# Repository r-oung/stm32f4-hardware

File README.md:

# Electronics EAGLE
A collection of [EAGLE](http://eagle.autodesk.com/) PCB projects.

## Organization
```
stm32f4-hardware       Root directory
├── assets             Custom EAGLE assets
|   ├── cam            CAM jobs
|   ├── dru            Design rules
|   ├── lbr            Libraries
|   ├── scr            Scripts
│   └── ulp            User language programs
└── prj                Projects
```

## Setup
In EAGLE's Control Panel, select `Options` > `Directories` and re-assign all directories with the ones in this repository.

## Licenses
Unless otherwise indicated in the file and/or folder, all files are licensed under [Creative Commons - Attribution 4.0 International (CC BY 4.0)](https://creativecommons.org/licenses/by/4.0/).

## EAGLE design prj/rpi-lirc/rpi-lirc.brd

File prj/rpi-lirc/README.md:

# Raspberry Pi LIRC Transceiver
A simple IR receiver and transceiver for the Raspberry Pi.

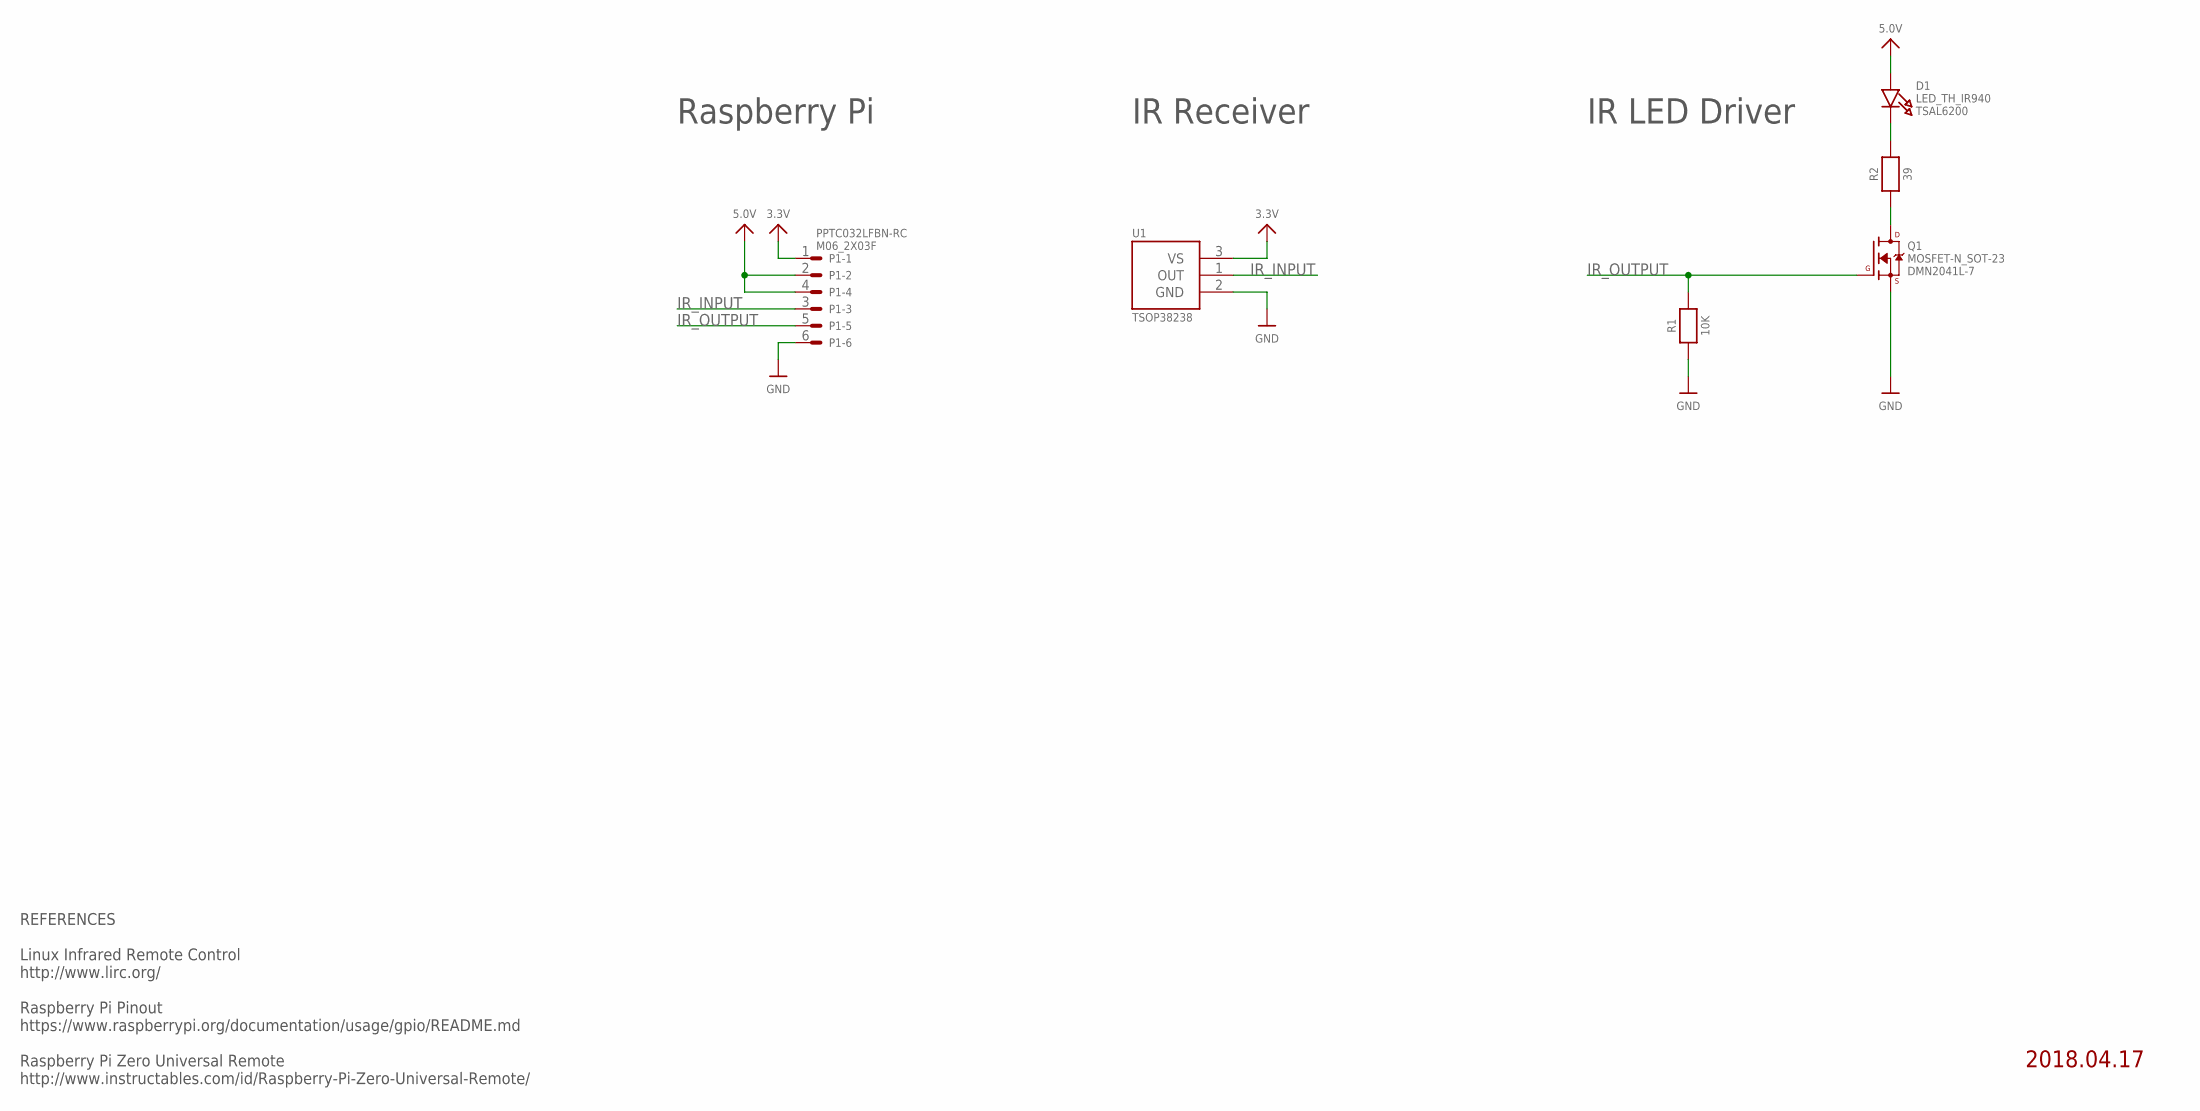
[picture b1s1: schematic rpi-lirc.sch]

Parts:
D1: LED_TH_IR940; RADIAL_5MM
P1: M06_2X03F; 2X03_LOCK
Q1: MOSFET-N_SOT-23; SOT23-3
R1: 10K; 0603
R2: 39; 0603
U1: TSOP38238

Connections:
3.3V: P1.1, U1.3 (VS)
5.0V: D1.A, P1.2, P1.4
GND: P1.6, Q1.2 (S), R1.1, U1.2 (GND)
IR_INPUT: P1.3, U1.1 (OUT)
IR_OUTPUT: P1.5, Q1.1 (G), R1.2
unnamed: D1.C, R2.2
unnamed: Q1.3 (D), R2.1

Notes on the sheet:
IR LED Driver
IR Receiver
Raspberry Pi
REFERENCES Linux Infrared Remote Control http://www.lirc.org/ Raspberry Pi Pinout https://www.raspberrypi.org/documentation/usage/gpio/README.md Raspberry Pi Zero Universal Remote http://www.instructables.com/id/Raspberry-Pi-Zero-Universal-Remote/
2018.04.17

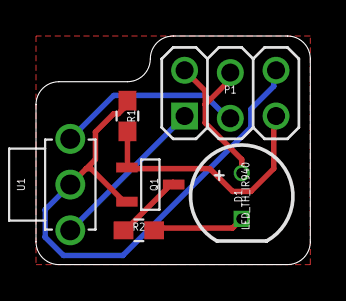
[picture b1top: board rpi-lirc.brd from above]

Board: 2 copper layers, 15.2 x 12.7 mm, 6 parts (0 on the bottom side), 7 nets.

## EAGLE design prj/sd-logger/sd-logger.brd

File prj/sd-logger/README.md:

# SD Logger
A tool for logging UART and CAN-bus data to an SD card.

The firmware for this project can be found in the [stm32f4-firmware repository](https://github.com/r-oung/stm32f4-firmware).

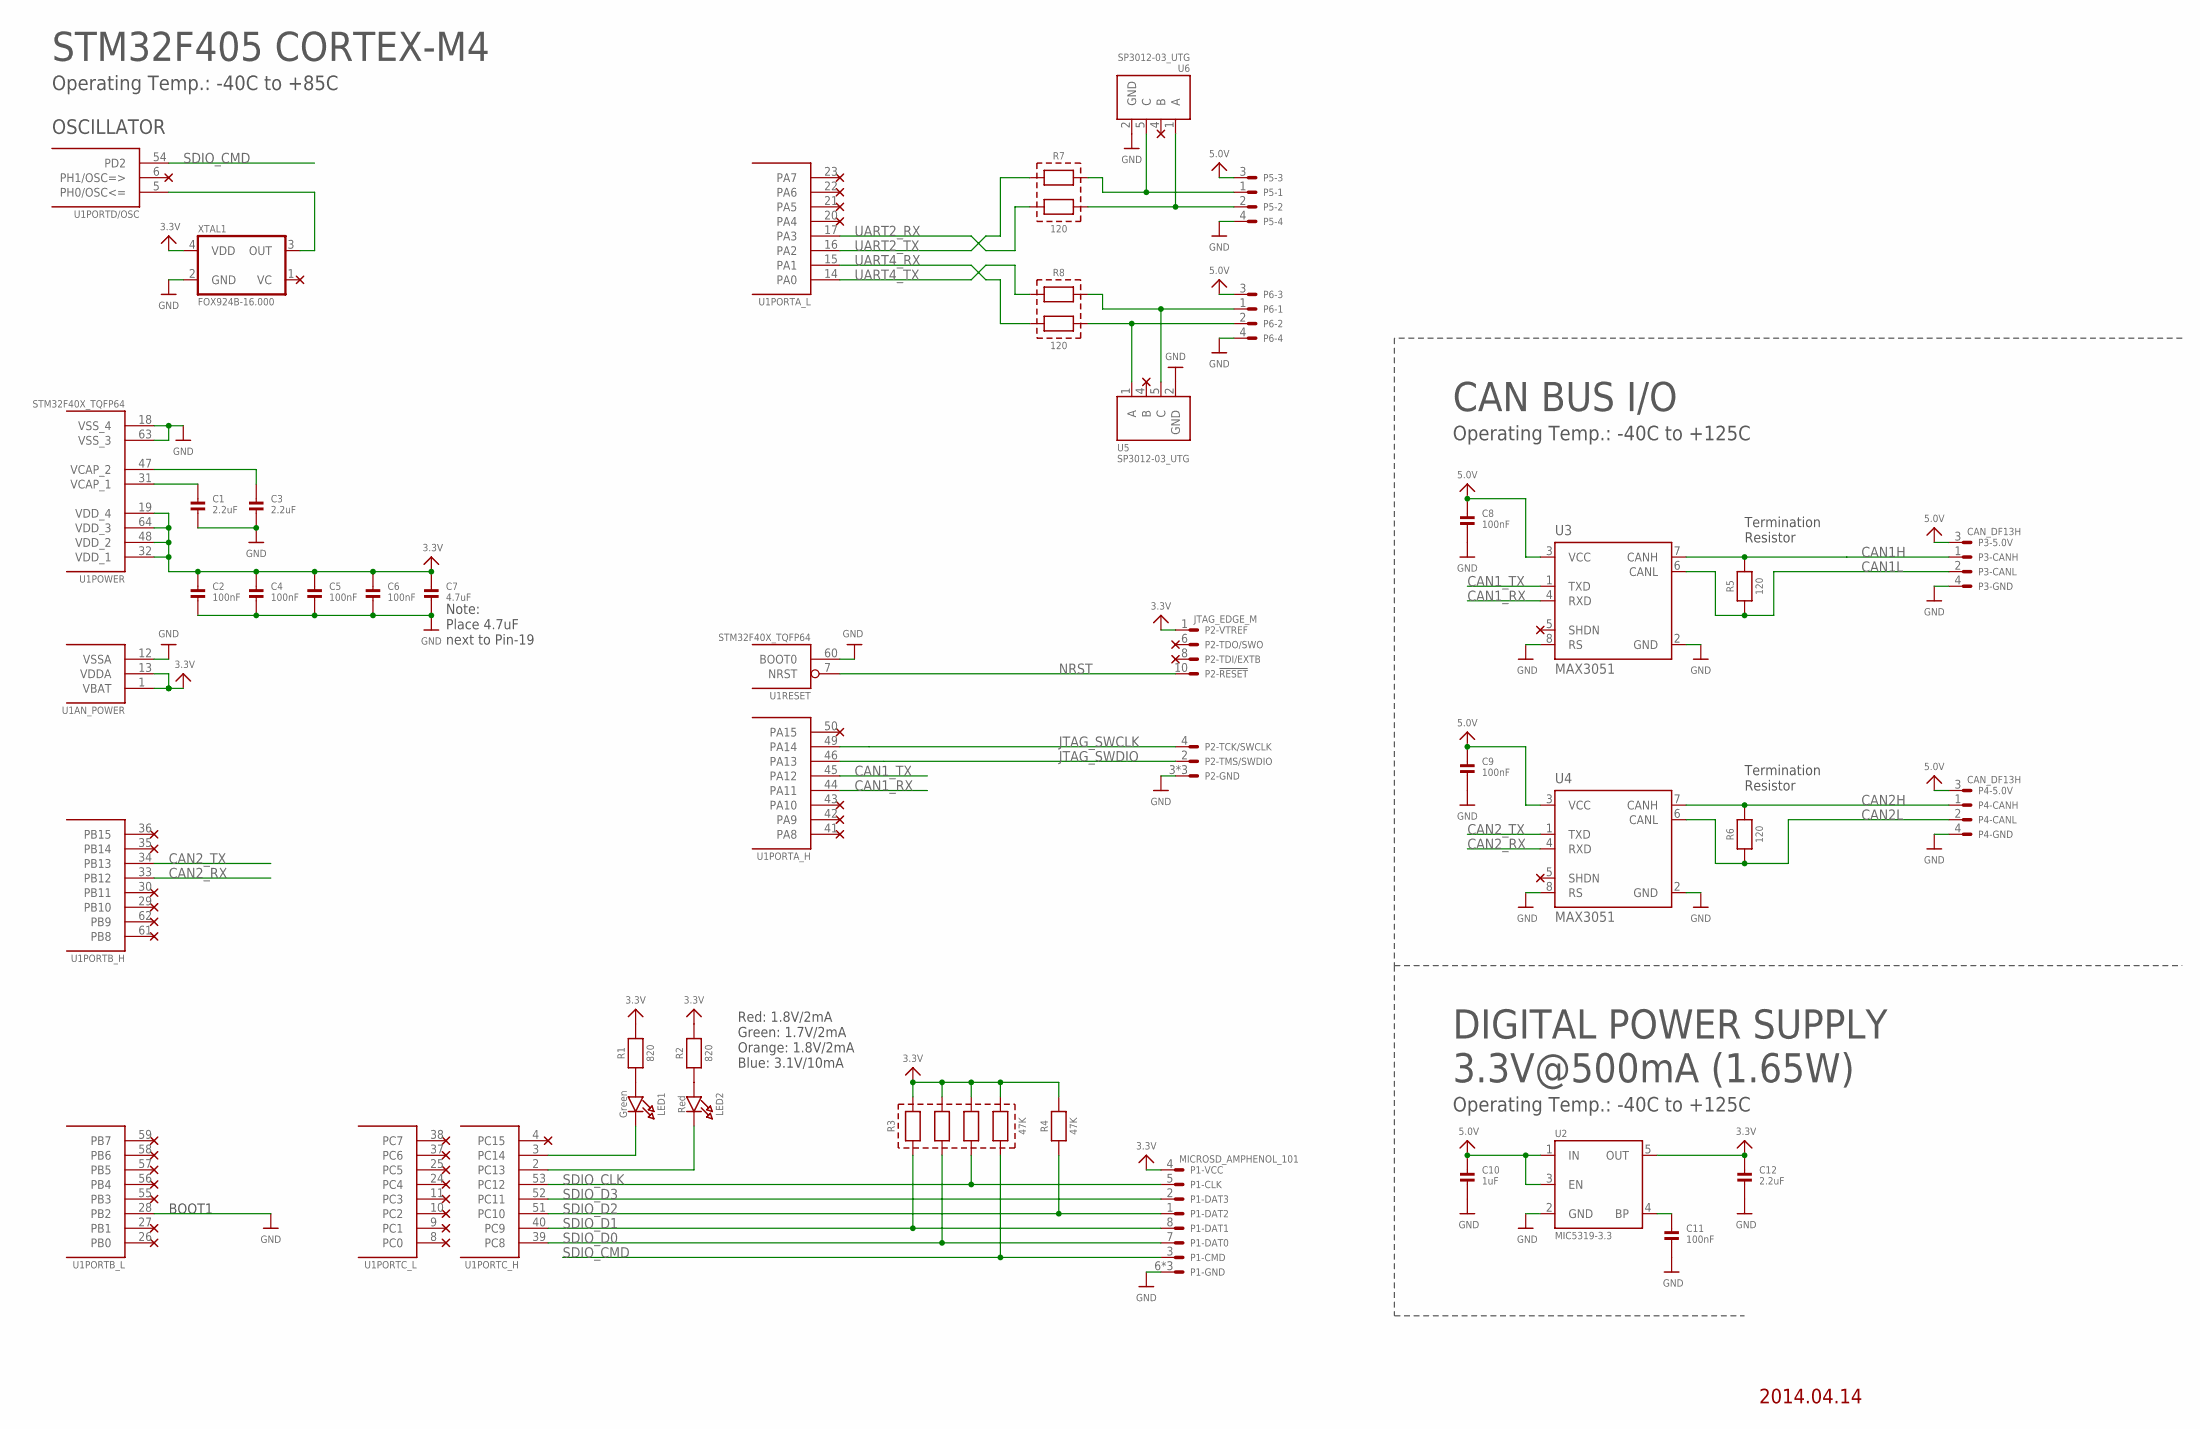
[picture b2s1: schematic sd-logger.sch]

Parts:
C1, C3, C12: 2.2uF; 0402
C2, C4, C5, C6, C8, C9, C11: 100nF; 0402
C7: 4.7uF; 0402
C10: 1uF; 0402
LED1: Green; CHIPLED_0603
LED2: Red; CHIPLED_0603
P1: MICROSD_AMPHENOL_101; AMPHENOL_101-00660-68
P2: JTAG_EDGE_M; FTSH-105-01-XXX-DV-EDGE
P3, P4: CAN_DF13H; DF13A-4P-1.25H
P5, P6: M04_DF13H; DF13A-4P-1.25H
R1, R2: 820; 0402
R3: 47K; EXBV8V
R4: 47K; 0402
R5, R6: 120; 0603
R7, R8: 120; EXBV4V
U1: STM32F40X_TQFP64; TQFP64
U2: MIC5319-3.3; SOT23-5
U3, U4: MAX3051; SOT23-8
U5, U6: SP3012-03_UTG; UDFN06
XTAL1: FOX924B-16.000; OSCILLATOR-5.0X3.2

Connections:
3.3V: C2.1, C4.1, C5.1, C6.1, C7.1, C12.1, P1.4, P2.1, R1.2, R2.2, R3.5, R3.6, R3.7, R3.8, R4.2, U1.1 (VBAT), U1.13 (VDDA), U1.19 (VDD_4), U1.32 (VDD_1), U1.48 (VDD_2), U1.64 (VDD_3), U2.5 (OUT), XTAL1.4 (VDD)
5.0V: C8.1, C9.1, C10.1, P3.3, P4.3, P5.3, P6.3, U2.1 (IN), U2.3 (EN), U3.3 (VCC), U4.3 (VCC)
CAN1H: P3.1, R5.2, U3.7 (CANH)
CAN1L: P3.2, R5.1, U3.6 (CANL)
CAN1_RX: U1.44 (PA11), U3.4 (RXD)
CAN1_TX: U1.45 (PA12), U3.1 (TXD)
CAN2H: P4.1, R6.2, U4.7 (CANH)
CAN2L: P4.2, R6.1, U4.6 (CANL)
CAN2_RX: U1.33 (PB12), U4.4 (RXD)
CAN2_TX: U1.34 (PB13), U4.1 (TXD)
GND: C1.2, C2.2, C3.2, C4.2, C5.2, C6.2, C7.2, C8.2, C9.2, C10.2, C11.2, C12.2, P1.6, P1.GND1, P1.GND3, P2.3, P2.5, P2.9, P3.4, P4.4, P5.4, P6.4, U1.12 (VSSA), U1.18 (VSS_4), U1.28 (PB2), U1.60 (BOOT0), U1.63 (VSS_3), U2.2 (GND), U3.2 (GND), U3.8 (RS), U4.2 (GND), U4.8 (RS), U5.2 (GND), U6.2 (GND), XTAL1.2 (GND)
JTAG_SWCLK: P2.4, U1.49 (PA14)
JTAG_SWDIO: P2.2, U1.46 (PA13)
unnamed: P5.2, R7.3, U6.1 (A)
unnamed: LED1.C, U1.3 (PC14)
unnamed: U1.5 (PH0/OSC<=), XTAL1.3 (OUT)
unnamed: C11.1, U2.4 (BP)
unnamed: P5.1, R7.4, U6.5 (C)
unnamed: P6.2, R8.3, U5.1 (A)
unnamed: P6.1, R8.4, U5.5 (C)
unnamed: LED2.C, U1.2 (PC13)
unnamed: LED2.A, R2.1
unnamed: LED1.A, R1.1
NRST: P2.10, U1.7 (NRST)
SDIO_CLK: P1.5, R3.3, U1.53 (PC12)
SDIO_CMD: P1.3, R3.4, U1.54 (PD2)
SDIO_D0: P1.7, R3.2, U1.39 (PC8)
SDIO_D1: P1.8, R3.1, U1.40 (PC9)
SDIO_D2: P1.1, R4.1, U1.51 (PC10)
SDIO_D3: P1.2, U1.52 (PC11)
UART2_RX: R7.2, U1.17 (PA3)
UART2_TX: R7.1, U1.16 (PA2)
UART4_RX: R8.2, U1.15 (PA1)
UART4_TX: R8.1, U1.14 (PA0)
VCAP_3: C3.1, U1.47 (VCAP_2)
VCAP_4: C1.1, U1.31 (VCAP_1)

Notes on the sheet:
STM32F405 CORTEX-M4
Operating Temp.: -40C to +85C
OSCILLATOR
BOOT1
Red: 1.8V/2mA Green: 1.7V/2mA Orange: 1.8V/2mA Blue: 3.1V/10mA
Note: Place 4.7uF next to Pin-19
DIGITAL POWER SUPPLY 3.3V@500mA (1.65W)
Operating Temp.: -40C to +125C
CAN BUS I/O
Termination Resistor
2014.04.14

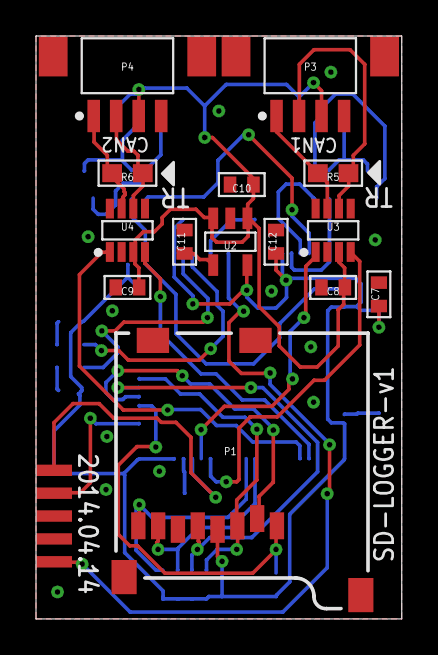
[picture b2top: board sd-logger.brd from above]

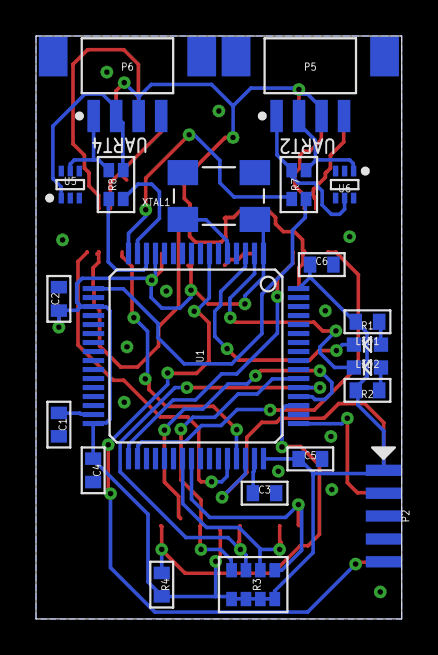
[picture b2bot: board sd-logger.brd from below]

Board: 2 copper layers, 20.3 x 32.4 mm, 35 parts (21 on the bottom side), 36 nets.

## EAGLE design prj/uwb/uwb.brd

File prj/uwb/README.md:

# Ultra-Wideband Positioning System Node
A UWB node using the STM32F4 microcontroller and DecaWave DWM1000 module that can be used for communication, distance measurement, and positioning.

The firmware for this project can be found in the [stm32f4-firmware repository](https://github.com/r-oung/stm32f4-firmware).

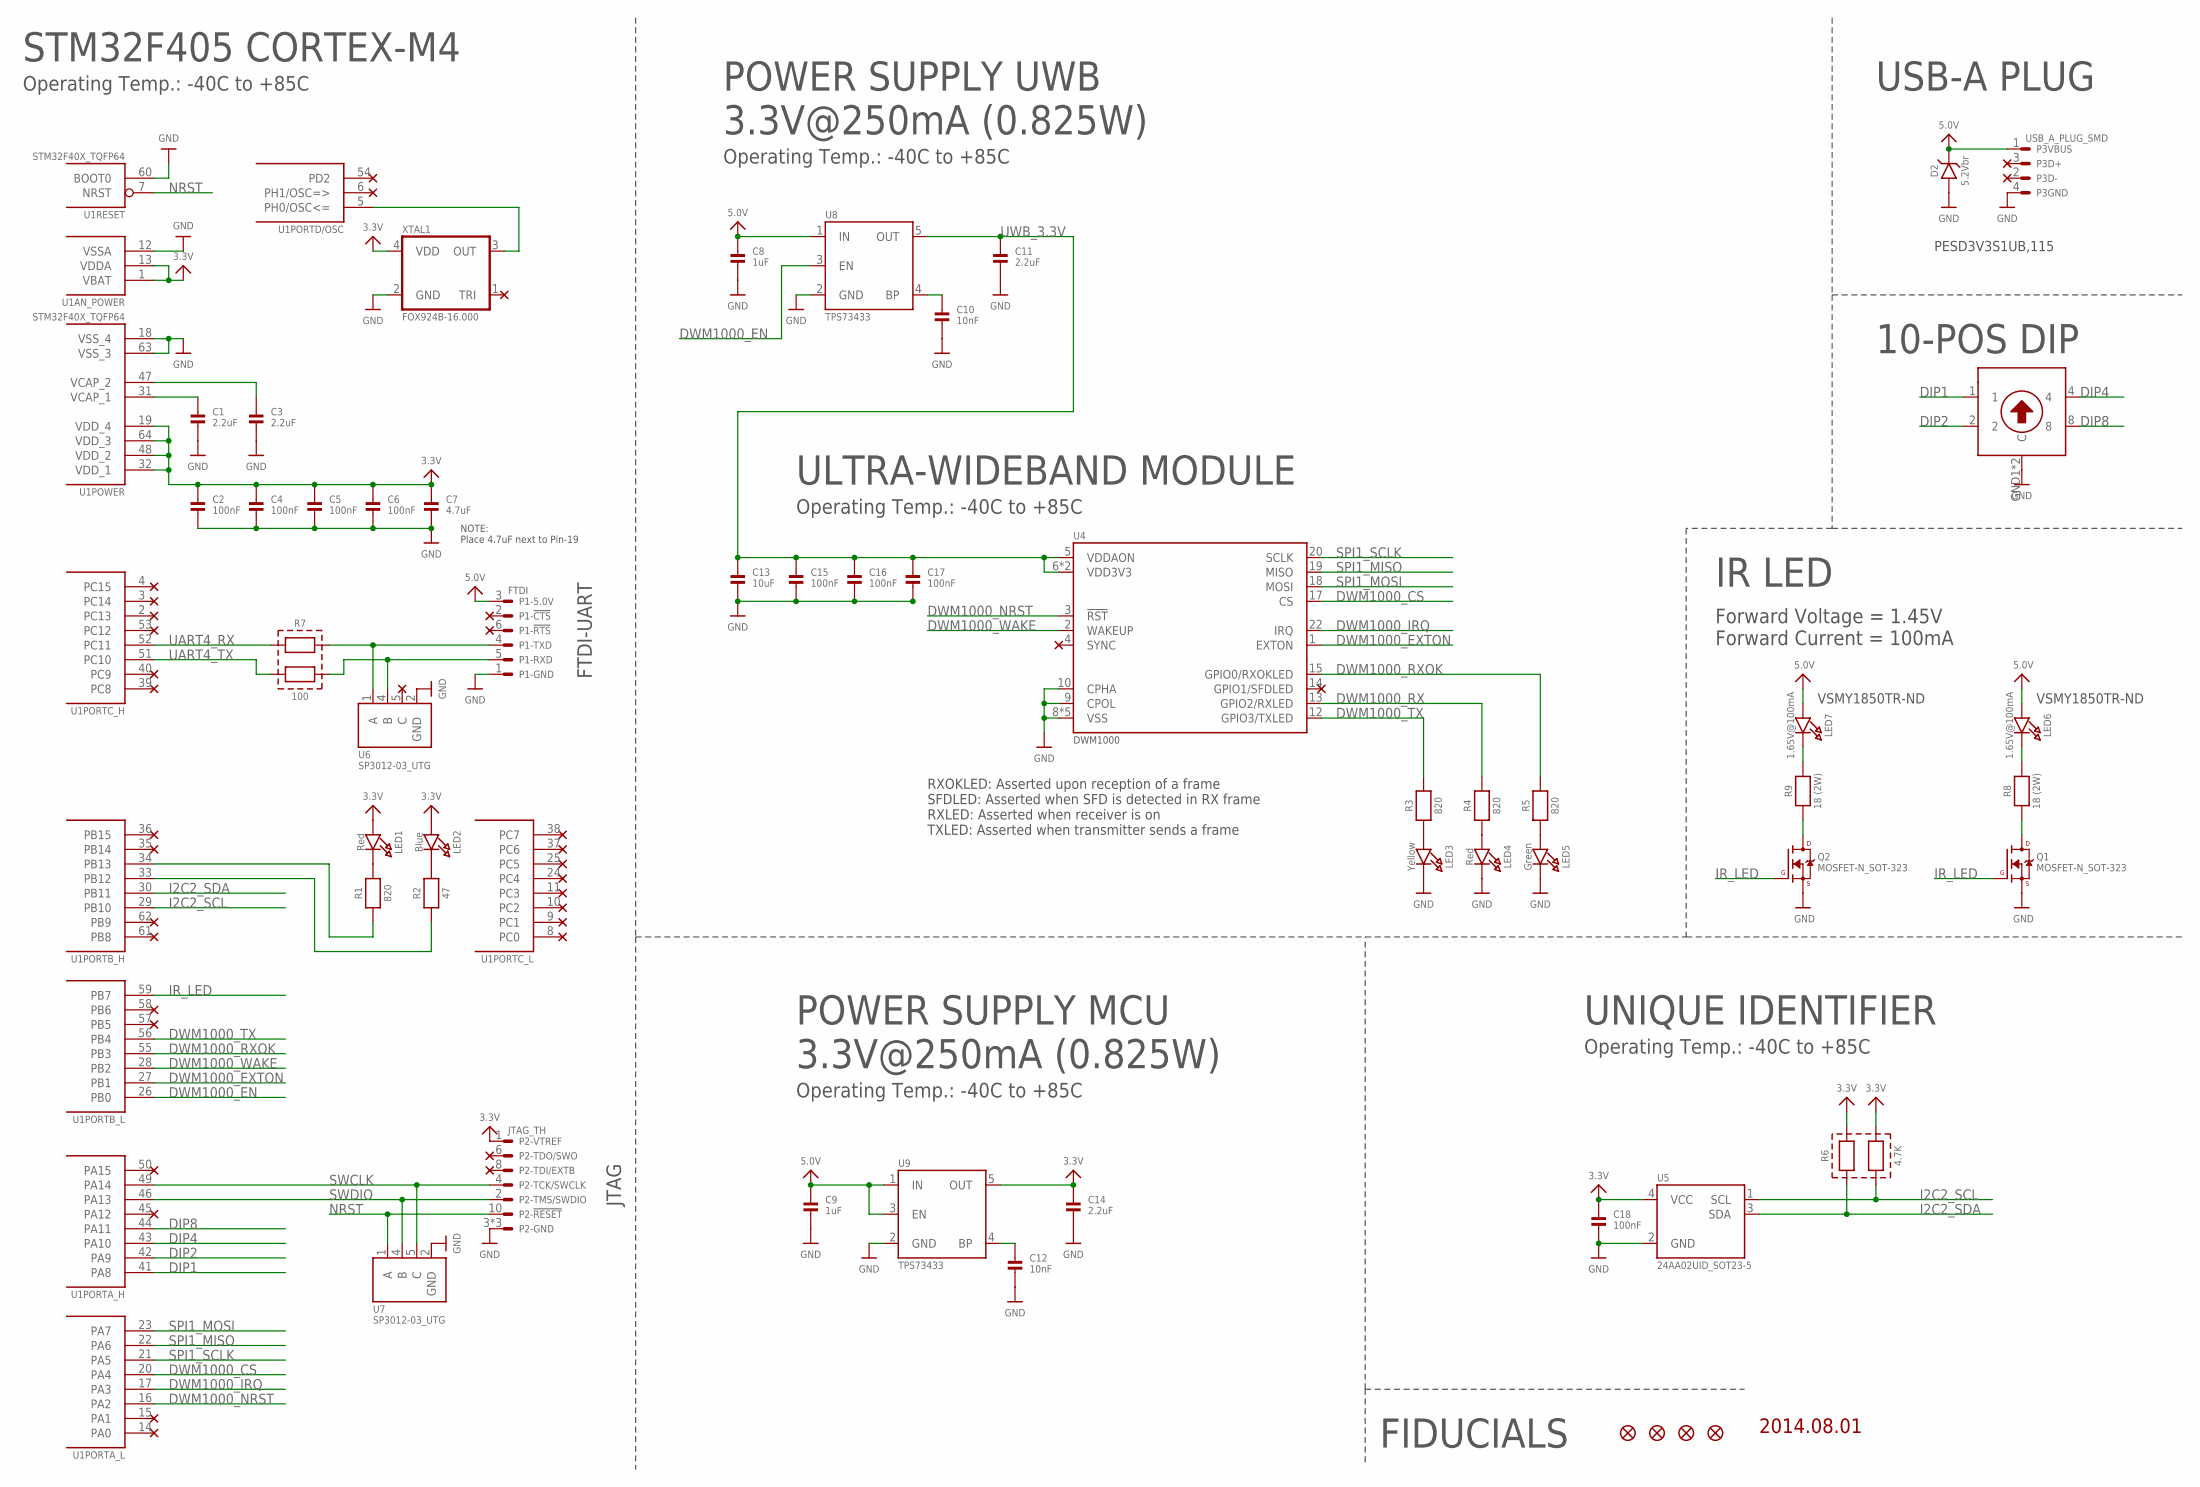
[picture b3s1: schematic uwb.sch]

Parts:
C1, C3, C11, C14: 2.2uF; 0402
C2, C4, C5, C6, C15, C16, C17, C18: 100nF; 0402
C7: 4.7uF; 0402
C8, C9: 1uF; 0402
C10, C12: 10nF; 0402
C13: 10uF; 0603
D2: 5.2Vbr; SOD-523
LED1, LED4: Red; CHIPLED_0603
LED2: Blue; CHIPLED_0603
LED3: Yellow; CHIPLED_0603
LED5: Green; CHIPLED_0603
LED6, LED7: 1.65V@100mA; CHIPLED_0805
P1: FTDI; 1X06_LOCK
P2: JTAG_TH; FTSH-105-01-XXX-DV
P3: USB_A_PLUG_SMD; USB-A_SMD
P4: DIP10_SH-7000B; SH-7000B
Q1, Q2: MOSFET-N_SOT-323; SOT323
R1, R3, R4, R5: 820; 0402
R2: 47; 0402
R6: 4.7K; EXBV4V
R7: 100; EXBV4V
R8, R9: 18 (2W); 2512
REF1, REF2, REF3, REF4: FIDUCIAL1X2.5; POINT-1MM
U1: STM32F40X_TQFP64; TQFP64
U4: DWM1000
U5: 24AA02UID_SOT23-5; SOT23-5
U6, U7: SP3012-03_UTG; UDFN06
U8, U9: TPS73433; SOT23-5
XTAL1: FOX924B-16.000; OSCILLATOR-5.0X3.2A

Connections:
3.3V: C2.1, C4.1, C5.1, C6.1, C7.1, C14.1, C18.1, LED1.A, LED2.A, P2.1, R6.3, R6.4, U1.1 (VBAT), U1.13 (VDDA), U1.19 (VDD_4), U1.32 (VDD_1), U1.48 (VDD_2), U1.64 (VDD_3), U5.4 (VCC), U9.5 (OUT), XTAL1.4 (VDD)
5.0V: C8.1, C9.1, D2.K (C), LED6.A, LED7.A, P1.3, P3.1, U8.1 (IN), U9.1 (IN), U9.3 (EN)
DIP1: P4.1, U1.41 (PA8)
DIP2: P4.2, U1.42 (PA9)
DIP4: P4.4, U1.43 (PA10)
DIP8: P4.8, U1.44 (PA11)
DWM1000_CS: U1.20 (PA4), U4.17 (CS)
DWM1000_EN: U1.26 (PB0), U8.3 (EN)
DWM1000_EXTON: U1.27 (PB1), U4.1 (EXTON)
DWM1000_IRQ: U1.17 (PA3), U4.22 (IRQ)
DWM1000_NRST: U1.16 (PA2), U4.3 (!RST)
DWM1000_RX: R4.2, U4.13 (GPIO2/RXLED)
DWM1000_RXOK: R5.2, U1.55 (PB3), U4.15 (GPIO0/RXOKLED)
DWM1000_TX: R3.2, U1.56 (PB4), U4.12 (GPIO3/TXLED)
DWM1000_WAKE: U1.28 (PB2), U4.2 (WAKEUP)
GND: C1.2, C2.2, C3.2, C4.2, C5.2, C6.2, C7.2, C8.2, C9.2, C10.2, C11.2, C12.2, C13.2, C14.2, C15.2, C16.2, C17.2, C18.2, D2.A, LED3.C, LED4.C, LED5.C, P1.1, P2.3, P2.5, P2.9, P3.4, P4.GND1 (C), P4.GND2 (C), Q1.2 (S), Q2.2 (S), U1.12 (VSSA), U1.18 (VSS_4), U1.60 (BOOT0), U1.63 (VSS_3), U4.8 (VSS), U4.9 (CPOL), U4.10 (CPHA), U4.16 (VSS), U4.21 (VSS), U4.23 (VSS), U4.24 (VSS), U5.2 (GND), U6.2 (GND), U7.2 (GND), U8.2 (GND), U9.2 (GND), XTAL1.2 (GND)
I2C2_SCL: R6.2, U1.29 (PB10), U5.1 (SCL)
I2C2_SDA: R6.1, U1.30 (PB11), U5.3 (SDA)
IR_LED: Q1.1 (G), Q2.1 (G), U1.59 (PB7)
unnamed: LED3.A, R3.1
unnamed: LED4.A, R4.1
unnamed: R2.1, U1.33 (PB12)
unnamed: C10.1, U8.4 (BP)
unnamed: LED1.C, R1.2
unnamed: R1.1, U1.34 (PB13)
unnamed: P1.5, R7.3, U6.4 (B)
unnamed: P1.4, R7.4, U6.1 (A)
unnamed: Q1.3 (D), R8.1
unnamed: LED6.C, R8.2
unnamed: Q2.3 (D), R9.1
unnamed: LED7.C, R9.2
unnamed: LED5.A, R5.1
unnamed: U1.5 (PH0/OSC<=), XTAL1.3 (OUT)
unnamed: LED2.C, R2.2
unnamed: C12.1, U9.4 (BP)
NRST: P2.10, U1.7 (NRST), U7.1 (A)
SPI1_MISO: U1.22 (PA6), U4.19 (MISO)
SPI1_MOSI: U1.23 (PA7), U4.18 (MOSI)
SPI1_SCLK: U1.21 (PA5), U4.20 (SCLK)
SWCLK: P2.4, U1.49 (PA14), U7.5 (C)
SWDIO: P2.2, U1.46 (PA13), U7.4 (B)
UART4_RX: R7.1, U1.52 (PC11)
UART4_TX: R7.2, U1.51 (PC10)
UWB_3.3V: C11.1, C13.1, C15.1, C16.1, C17.1, U4.5 (VDDAON), U4.6 (VDD3V3), U4.7 (VDD3V3), U8.5 (OUT)
VCAP_1: C1.1, U1.31 (VCAP_1)
VCAP_2: C3.1, U1.47 (VCAP_2)

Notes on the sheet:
POWER SUPPLY MCU 3.3V@250mA (0.825W)
Operating Temp.: -40C to +85C
ULTRA-WIDEBAND MODULE
RXOKLED: Asserted upon reception of a frame SFDLED: Asserted when SFD is detected in RX frame RXLED: Asserted when receiver is on TXLED: Asserted when transmitter sends a frame
STM32F405 CORTEX-M4
NOTE: Place 4.7uF next to Pin-19
POWER SUPPLY UWB 3.3V@250mA (0.825W)
UNIQUE IDENTIFIER
JTAG
FTDI-UART
USB-A PLUG
PESD3V3S1UB,115
FIDUCIALS
10-POS DIP
IR LED
Forward Voltage = 1.45V Forward Current = 100mA
VSMY1850TR-ND
2014.08.01

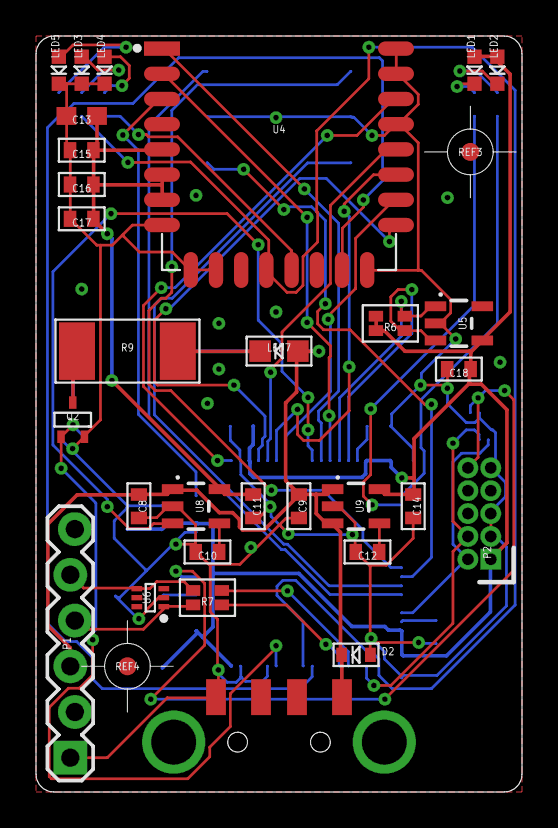
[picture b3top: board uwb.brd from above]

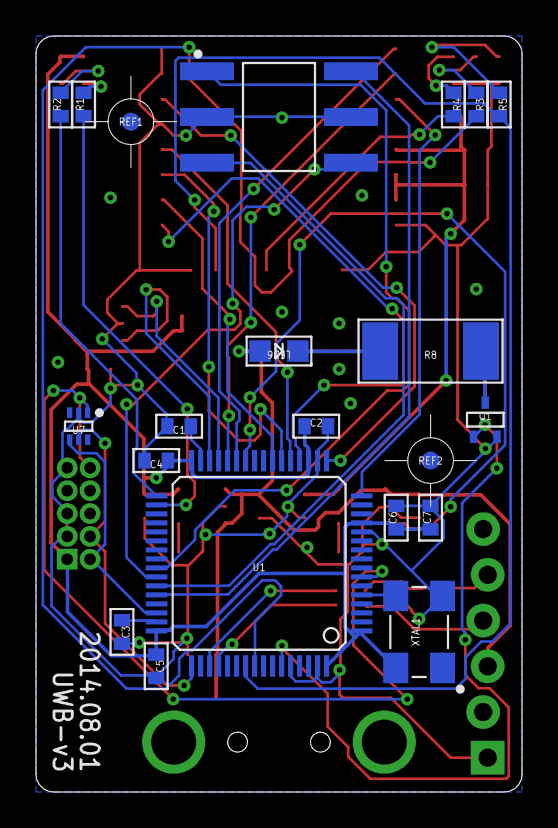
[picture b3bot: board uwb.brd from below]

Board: 2 copper layers, 27.0 x 42.0 mm, 53 parts (21 on the bottom side), 46 nets.

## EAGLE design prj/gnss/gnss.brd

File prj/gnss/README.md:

# GNSS
A global navigation satellite navigation system with CAN-bus communication, using the STM32F4 microcontroller and uBlox NEO8 GNSS receiver.

The firmware for this project can be found in the [stm32f4-firmware repository](https://github.com/r-oung/stm32f4-firmware).

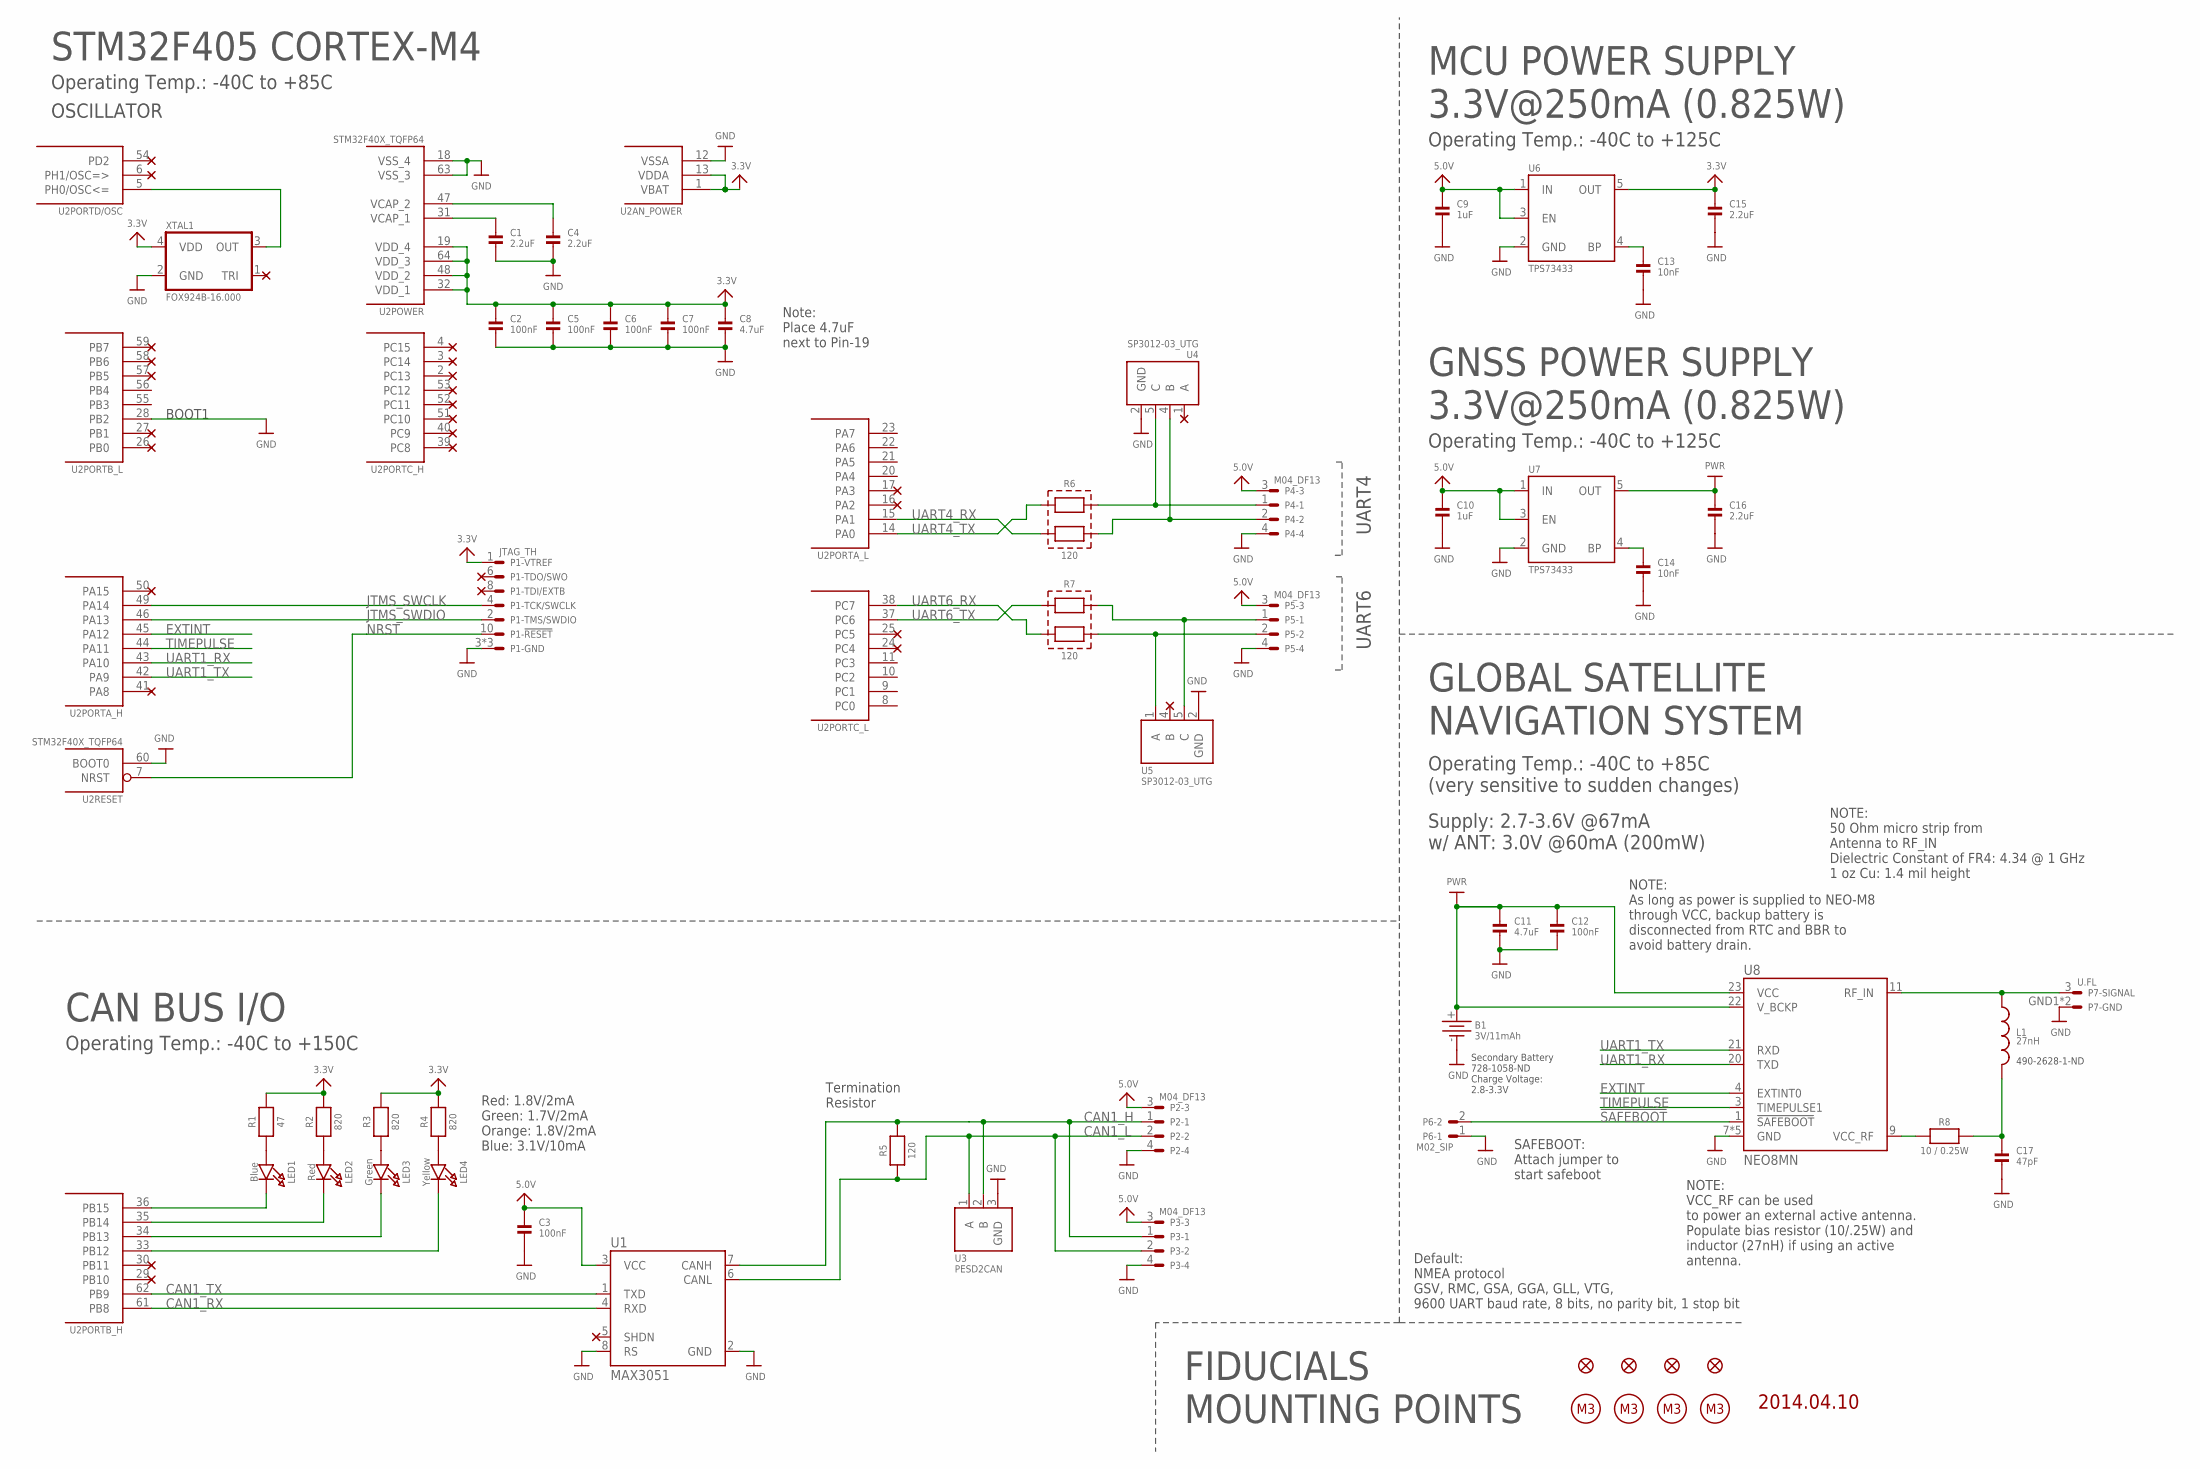
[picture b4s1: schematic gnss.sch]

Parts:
B1: 3V/11mAh; MS920SE
C1, C4, C15, C16: 2.2uF; 0402
C2, C3, C5, C6, C7, C12: 100nF; 0402
C8, C11: 4.7uF; 0402
C9, C10: 1uF; 0402
C13, C14: 10nF; 0402
C17: 47pF; 0402
L1: 27nH; L0402
LED1: Blue; CHIPLED_0603
LED2: Red; CHIPLED_0603
LED3: Green; CHIPLED_0603
LED4: Yellow; CHIPLED_0603
MP1, MP2, MP3, MP4: M3; MP_M3
P1: JTAG_TH; FTSH-105-01-XXX-DV
P2, P3, P4, P5: M04_DF13; DF13A-4P-1.25H
P6: M02_SIP; 1X02_LOCK
P7: U.FL
R1: 47; 0402
R2, R3, R4: 820; 0402
R5: 120; 0603
R6, R7: 120; EXBV4V
R8: 10 / 0.25W; 0603
REF1, REF2, REF3, REF4: FIDUCIAL1X2.5; POINT-1MM
U1: MAX3051; SOT23-8
U2: STM32F40X_TQFP64; TQFP64
U3: PESD2CAN; SOT23-3
U4, U5: SP3012-03_UTG; UDFN06
U6, U7: TPS73433; SOT23-5
U8: NEO8MN; NEOX
XTAL1: FOX924B-16.000; OSCILLATOR-5.0X3.2A

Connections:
3.3V: C2.1, C5.1, C6.1, C7.1, C8.1, C15.1, P1.1, R1.2, R2.2, R3.2, R4.2, U2.1 (VBAT), U2.13 (VDDA), U2.19 (VDD_4), U2.32 (VDD_1), U2.48 (VDD_2), U2.64 (VDD_3), U6.5 (OUT), XTAL1.4 (VDD)
5.0V: C3.1, C9.1, C10.1, P2.3, P3.3, P4.3, P5.3, U1.3 (VCC), U6.1 (IN), U6.3 (EN), U7.1 (IN), U7.3 (EN)
!SAFEBOOT: P6.2, U8.1 (!SAFEBOOT)
CAN1_H: P2.1, P3.1, R5.2, U1.7 (CANH), U3.2 (B)
CAN1_L: P2.2, P3.2, R5.1, U1.6 (CANL), U3.1 (A)
CAN1_RX: U1.4 (RXD), U2.61 (PB8)
CAN1_TX: U1.1 (TXD), U2.62 (PB9)
EXTINT: U2.45 (PA12), U8.4 (EXTINT0)
GND: B1.-, C1.2, C2.2, C3.2, C4.2, C5.2, C6.2, C7.2, C8.2, C9.2, C10.2, C11.2, C12.2, C13.2, C14.2, C15.2, C16.2, C17.2, P1.3, P1.5, P1.9, P2.4, P3.4, P4.4, P5.4, P6.1, P7.GND1, P7.GND2, U1.2 (GND), U1.8 (RS), U2.12 (VSSA), U2.18 (VSS_4), U2.28 (PB2), U2.60 (BOOT0), U2.63 (VSS_3), U3.3 (GND), U4.2 (GND), U5.2 (GND), U6.2 (GND), U7.2 (GND), U8.7 (GND), U8.10 (GND), U8.12 (GND), U8.13 (GND), U8.24 (GND), XTAL1.2 (GND)
JTMS_SWCLK: P1.4, U2.49 (PA14)
JTMS_SWDIO: P1.2, U2.46 (PA13)
unnamed: LED2.A, R2.1
unnamed: LED3.A, R3.1
unnamed: LED4.A, R4.1
unnamed: L1.1, P7.3, U8.11 (RF_IN)
unnamed: LED1.A, R1.1
unnamed: R8.1, U8.9 (VCC_RF)
unnamed: LED1.C, U2.36 (PB15)
unnamed: U2.5 (PH0/OSC<=), XTAL1.3 (OUT)
unnamed: C13.1, U6.4 (BP)
unnamed: LED2.C, U2.35 (PB14)
unnamed: LED3.C, U2.34 (PB13)
unnamed: LED4.C, U2.33 (PB12)
unnamed: C14.1, U7.4 (BP)
unnamed: C17.1, L1.2, R8.2
NRST: P1.10, U2.7 (NRST)
PWR: B1.+, C11.1, C12.1, C16.1, U7.5 (OUT), U8.22 (V_BCKP), U8.23 (VCC)
P_UART4_RX: P4.2, R6.3, U4.4 (B)
P_UART4_TX: P4.1, R6.4, U4.5 (C)
P_UART6_RX: P5.2, R7.3, U5.1 (A)
P_UART6_TX: P5.1, R7.4, U5.5 (C)
TIMEPULSE: U2.44 (PA11), U8.3 (TIMEPULSE1)
UART1_RX: U2.43 (PA10), U8.20 (TXD)
UART1_TX: U2.42 (PA9), U8.21 (RXD)
UART4_RX: R6.2, U2.15 (PA1)
UART4_TX: R6.1, U2.14 (PA0)
UART6_RX: R7.2, U2.38 (PC7)
UART6_TX: R7.1, U2.37 (PC6)
VCAP_1: C1.1, U2.31 (VCAP_1)
VCAP_2: C4.1, U2.47 (VCAP_2)

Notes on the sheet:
STM32F405 CORTEX-M4
Operating Temp.: -40C to +85C
OSCILLATOR
BOOT1
Red: 1.8V/2mA Green: 1.7V/2mA Orange: 1.8V/2mA Blue: 3.1V/10mA
Note: Place 4.7uF next to Pin-19
MCU POWER SUPPLY 3.3V@250mA (0.825W)
Operating Temp.: -40C to +125C
Operating Temp.: -40C to +150C
CAN BUS I/O
Termination Resistor
MOUNTING POINTS
FIDUCIALS
UART4
UART6
GLOBAL SATELLITE NAVIGATION SYSTEM
Operating Temp.: -40C to +85C (very sensitive to sudden changes)
Supply: 2.7-3.6V @67mA w/ ANT: 3.0V @60mA (200mW)
NOTE: VCC_RF can be used to power an external active antenna. Populate bias resistor (10/.25W) and inductor (27nH) if using an active antenna.
NOTE: 50 Ohm micro strip from Antenna to RF_IN Dielectric Constant of FR4: 4.34 @ 1 GHz 1 oz Cu: 1.4 mil height
Default: NMEA protocol GSV, RMC, GSA, GGA, GLL, VTG, 9600 UART baud rate, 8 bits, no parity bit, 1 stop bit
490-2628-1-ND
Secondary Battery 728-1058-ND Charge Voltage: 2.8-3.3V
GNSS POWER SUPPLY 3.3V@250mA (0.825W)
SAFEBOOT: Attach jumper to start safeboot
NOTE: As long as power is supplied to NEO-M8 through VCC, backup battery is disconnected from RTC and BBR to avoid battery drain.
2014.04.10

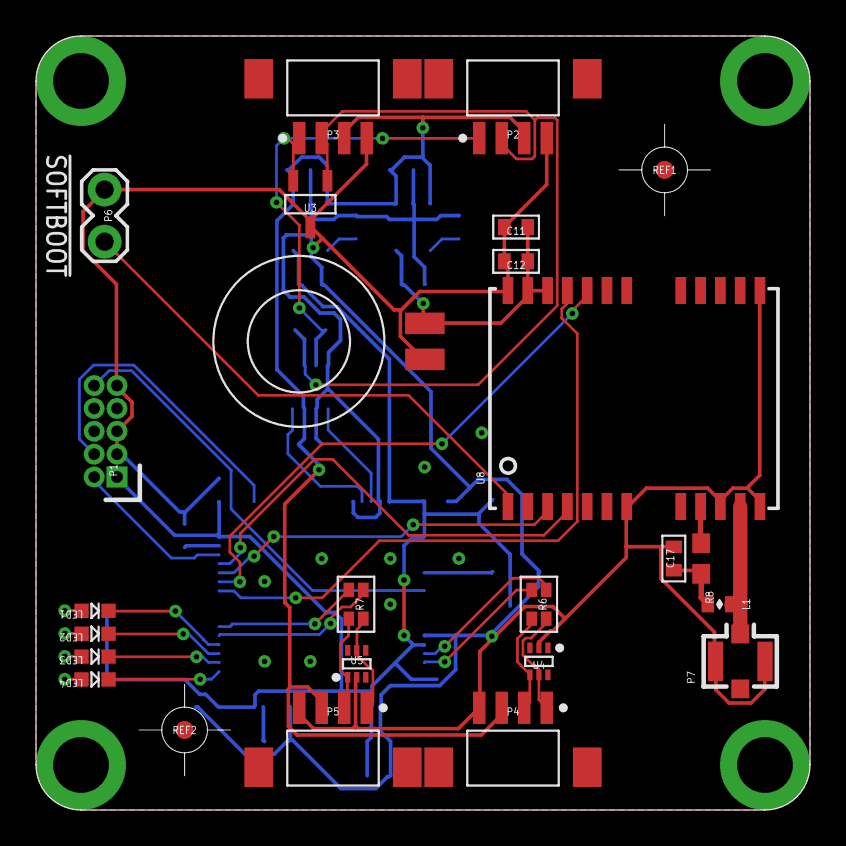
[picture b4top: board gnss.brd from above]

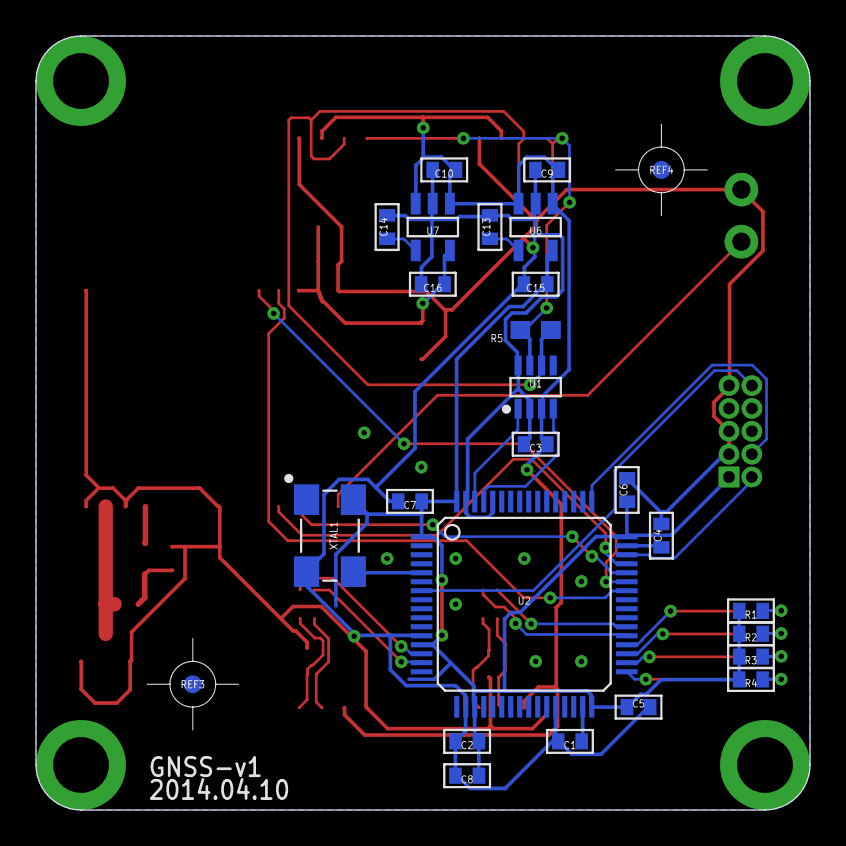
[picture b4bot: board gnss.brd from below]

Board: 2 copper layers, 43.0 x 43.0 mm, 55 parts (26 on the bottom side), 40 nets.
